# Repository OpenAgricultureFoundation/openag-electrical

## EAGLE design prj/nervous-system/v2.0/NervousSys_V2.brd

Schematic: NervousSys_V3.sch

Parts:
ATTRIBUTES: DOCFIELD
C1: 4.7uF; CAP_C1206
C2: 0.1uF; C0603
C3, C11: .1uF; C0603@1
C4: 4.7uF; C0805
C9: 10uF; C1206
D1: SMAJ14A; DO-214AC
D2, D3, D4: APT1608CGCK; CHIPLED_0603
F11: SST 7; SS
F12: GSH15
IC2, IC3, IC4, IC5, IC6, IC7, IC8, IC9: PCA9615DP; SOP50P490X110-10N
J1: 87583-2010BLF; CONN_USB-87583
J2, J3, J4, J5, J6, J7, J8, J9: 54602-908LF; OPENAG-V1-RJ45
R1, R22, R23, R30, R31, R38, R39, R46, R47, R54, R55, R62, R63, R70, R71, R78, R79: 10K; R0603
R2, R3, R4, R5, R6, R7, R8, R9: 10K; 0603-RES
R10: 200; RC0603N
R11: 560; RC0603N
R12: 4.3K; RC0603N
R13, R86, R87: 0 OHM; RC0603N
R16, R18, R19, R20, R24, R26, R27, R28, R32, R34, R35, R36, R40, R42, R43, R44, R48, R50, R51, R52, R56, R58, R59, R60, R64, R66, R67, R68, R72, R74, R75, R76: 600; R0603
R17, R21, R25, R29, R33, R37, R41, R45, R49, R53, R57, R61, R65, R69, R73, R77: 120; R0603
T1: R-78E5.0-1.0
U1: TCA9548APWRPW24-M; PW24-M
U2: PHOTONH; PHOTON
U$1, U$3: PJ-036AH
U$4: BBB_SMD; 23PINHEADERSMD

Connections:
24V_IN: F11.1, F12.1, U$1.1, U$3.1
+5V: C2.1, C4.1, IC2.10 (VDD_(B)), IC3.10 (VDD_(B)), IC4.10 (VDD_(B)), IC5.10 (VDD_(B)), IC6.10 (VDD_(B)), IC7.10 (VDD_(B)), IC8.10 (VDD_(B)), IC9.10 (VDD_(B)), R11.2, R18.1, R19.2, R26.1, R27.2, R34.1, R35.2, R42.1, R43.2, R50.1, R51.2, R58.1, R59.2, R66.1, R67.2, R74.1, R75.2, T1.3 (+VOUT), U2.1 (VIN), U$4.VDD5V; also elsewhere on the board
A0_EXT_1: R4.1, R5.2, U1.1 (A0)
A1_EXT_1: R6.1, R7.2, U1.2 (A1)
A2_EXT_1: R2.1, R3.2, U1.21 (A2)
DSCLM0: IC2.6 (DSCLM), J2.DSCLM(5) (DSCLM), R20.2, R21.1
DSCLM1: IC3.6 (DSCLM), J3.DSCLM(5) (DSCLM), R28.2, R29.1
DSCLM2: IC5.6 (DSCLM), J5.DSCLM(5) (DSCLM), R44.2, R45.1
DSCLM3: IC4.6 (DSCLM), J4.DSCLM(5) (DSCLM), R36.2, R37.1
DSCLM4: IC6.6 (DSCLM), J6.DSCLM(5) (DSCLM), R52.2, R53.1
DSCLM5: IC7.6 (DSCLM), J7.DSCLM(5) (DSCLM), R60.2, R61.1
DSCLM6: IC8.6 (DSCLM), J8.DSCLM(5) (DSCLM), R68.2, R69.1
DSCLM7: IC9.6 (DSCLM), J9.DSCLM(5) (DSCLM), R76.2, R77.1
DSCLP0: IC2.7 (DSCLP), J2.DSCLP(4) (DSCLP), R19.1, R21.2
DSCLP1: IC3.7 (DSCLP), J3.DSCLP(4) (DSCLP), R27.1, R29.2
DSCLP2: IC5.7 (DSCLP), J5.DSCLP(4) (DSCLP), R43.1, R45.2
DSCLP3: IC4.7 (DSCLP), J4.DSCLP(4) (DSCLP), R35.1, R37.2
DSCLP4: IC6.7 (DSCLP), J6.DSCLP(4) (DSCLP), R51.1, R53.2
DSCLP5: IC7.7 (DSCLP), J7.DSCLP(4) (DSCLP), R59.1, R61.2
DSCLP6: IC8.7 (DSCLP), J8.DSCLP(4) (DSCLP), R67.1, R69.2
DSCLP7: IC9.7 (DSCLP), J9.DSCLP(4) (DSCLP), R75.1, R77.2
DSDAM0: IC2.9 (DSDAM), J2.DSDAM(2) (DSDAM), R16.1, R17.2
DSDAM1: IC3.9 (DSDAM), J3.DSDAM(2) (DSDAM), R24.1, R25.2
DSDAM2: IC5.9 (DSDAM), J5.DSDAM(2) (DSDAM), R40.1, R41.2
DSDAM3: IC4.9 (DSDAM), J4.DSDAM(2) (DSDAM), R32.1, R33.2
DSDAM4: IC6.9 (DSDAM), J6.DSDAM(2) (DSDAM), R48.1, R49.2
DSDAM5: IC7.9 (DSDAM), J7.DSDAM(2) (DSDAM), R56.1, R57.2
DSDAM6: IC8.9 (DSDAM), J8.DSDAM(2) (DSDAM), R64.1, R65.2
DSDAM7: IC9.9 (DSDAM), J9.DSDAM(2) (DSDAM), R72.1, R73.2
DSDAP0: IC2.8 (DSDAP), J2.DSDAP(1) (DSDAP), R17.1, R18.2
DSDAP1: IC3.8 (DSDAP), J3.DSDAP(1) (DSDAP), R25.1, R26.2
DSDAP2: IC5.8 (DSDAP), J5.DSDAP(1) (DSDAP), R41.1, R42.2
DSDAP3: IC4.8 (DSDAP), J4.DSDAP(1) (DSDAP), R33.1, R34.2
DSDAP4: IC6.8 (DSDAP), J6.DSDAP(1) (DSDAP), R49.1, R50.2
DSDAP5: IC7.8 (DSDAP), J7.DSDAP(1) (DSDAP), R57.1, R58.2
DSDAP6: IC8.8 (DSDAP), J8.DSDAP(1) (DSDAP), R65.1, R66.2
DSDAP7: IC9.8 (DSDAP), J9.DSDAP(1) (DSDAP), R73.1, R74.2
GND: C1.2, C2.2, C3.2, C4.2, C9.2, C11.2, D1.A, D2.C, D3.C, D4.C, IC2.5 (VSS), IC3.5 (VSS), IC4.5 (VSS), IC5.5 (VSS), IC6.5 (VSS), IC7.5 (VSS), IC8.5 (VSS), IC9.5 (VSS), J1.1, J2.GND(3) (GND), J3.GND(3) (GND), J4.GND(3) (GND), J5.GND(3) (GND), J6.GND(3) (GND), J7.GND(3) (GND), J8.GND(3) (GND), J9.GND(3) (GND), R3.1, R5.1, R7.1, R16.2, R20.1, R24.2, R28.1, R32.2, R36.1, R40.2, R44.1, R48.2, R52.1, R56.2, R60.1, R64.2, R68.1, R72.2, R76.1, T1.2 (GND), U1.12 (GND), U2.2 (GND), U2.21 (GND), U$1.2, U$1.3, U$3.2, U$3.3, U$4.DGND; also elsewhere on the board
unnamed: D3.A, R11.1
unnamed: D4.A, R12.1
unnamed: D2.A, R10.1
PHOTON_A0: U2.12 (A0)
PHOTON_A1: U2.11 (A1)
PHOTON_D2: U2.15 (D2)
PHOTON_D3: U2.16 (D3)
PHOTON_D4: U2.17 (D4)
PHOTON_RX: U2.4 (RX)
PHOTON_SCL: R87.1, U2.14 (D1)
PHOTON_SDA: R86.1, U2.13 (D0)
PHOTON_TX: U2.3 (TX)
RESET1: R1.1, U1.3 (!RESET)
SC0: IC2.4 (SCL), R23.1, U1.5 (SC0)
SC1: IC3.4 (SCL), R31.1, U1.7 (SC1)
SC2: IC5.4 (SCL), R47.1, U1.9 (SC2)
SC3: IC4.4 (SCL), R39.1, U1.11 (SC3)
SC4: IC6.4 (SCL), R55.1, U1.14 (SC4)
SC5: IC7.4 (SCL), R63.1, U1.16 (SC5)
SC6: IC8.4 (SCL), R71.1, U1.18 (SC6)
SC7: IC9.4 (SCL), R79.1, U1.20 (SC7)
SCL: R8.1, R87.2, U1.22 (SCL); also elsewhere on the board
SD0: IC2.2 (SDA), R22.1, U1.4 (SD0)
SD1: IC3.2 (SDA), R30.1, U1.6 (SD1)
SD2: IC5.2 (SDA), R46.1, U1.8 (SD2)
SD3: IC4.2 (SDA), R38.1, U1.10 (SD3)
SD4: IC6.2 (SDA), R54.1, U1.13 (SD4)
SD5: IC7.2 (SDA), R62.1, U1.15 (SD5)
SD6: IC8.2 (SDA), R70.1, U1.17 (SD6)
SD7: IC9.2 (SDA), R78.1, U1.19 (SD7)
SDA: R9.1, R86.2, U1.23 (SDA); also elsewhere on the board
USBM0: J2.USBM(8) (USBM)
USBM1: J1.3, J3.USBM(8) (USBM)
USBM2: J5.USBM(8) (USBM)
USBM3: J4.USBM(8) (USBM)
USBM4: J6.USBM(8) (USBM)
USBM5: J7.USBM(8) (USBM)
USBM6: J8.USBM(8) (USBM)
USBM7: J9.USBM(8) (USBM)
USBP0: J2.USBP(7) (USBP)
USBP1: J1.2, J3.USBP(7) (USBP)
USBP2: J5.USBP(7) (USBP)
USBP3: J4.USBP(7) (USBP)
USBP4: J6.USBP(7) (USBP)
USBP5: J7.USBP(7) (USBP)
USBP6: J8.USBP(7) (USBP)
USBP7: J9.USBP(7) (USBP)
VBAT: U2.22 (VBAT)

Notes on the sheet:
Original Board by Dan Poitrast
Change Log:
I2C Pull-up Resistors
Released under the Creative Commons Attribution Share-Alike 4.0 License https://creativecommons.org/licenses/by-sa/4.0/
I2C Address Select IO Ext 1
Beaglebone Black Outline and throughholes

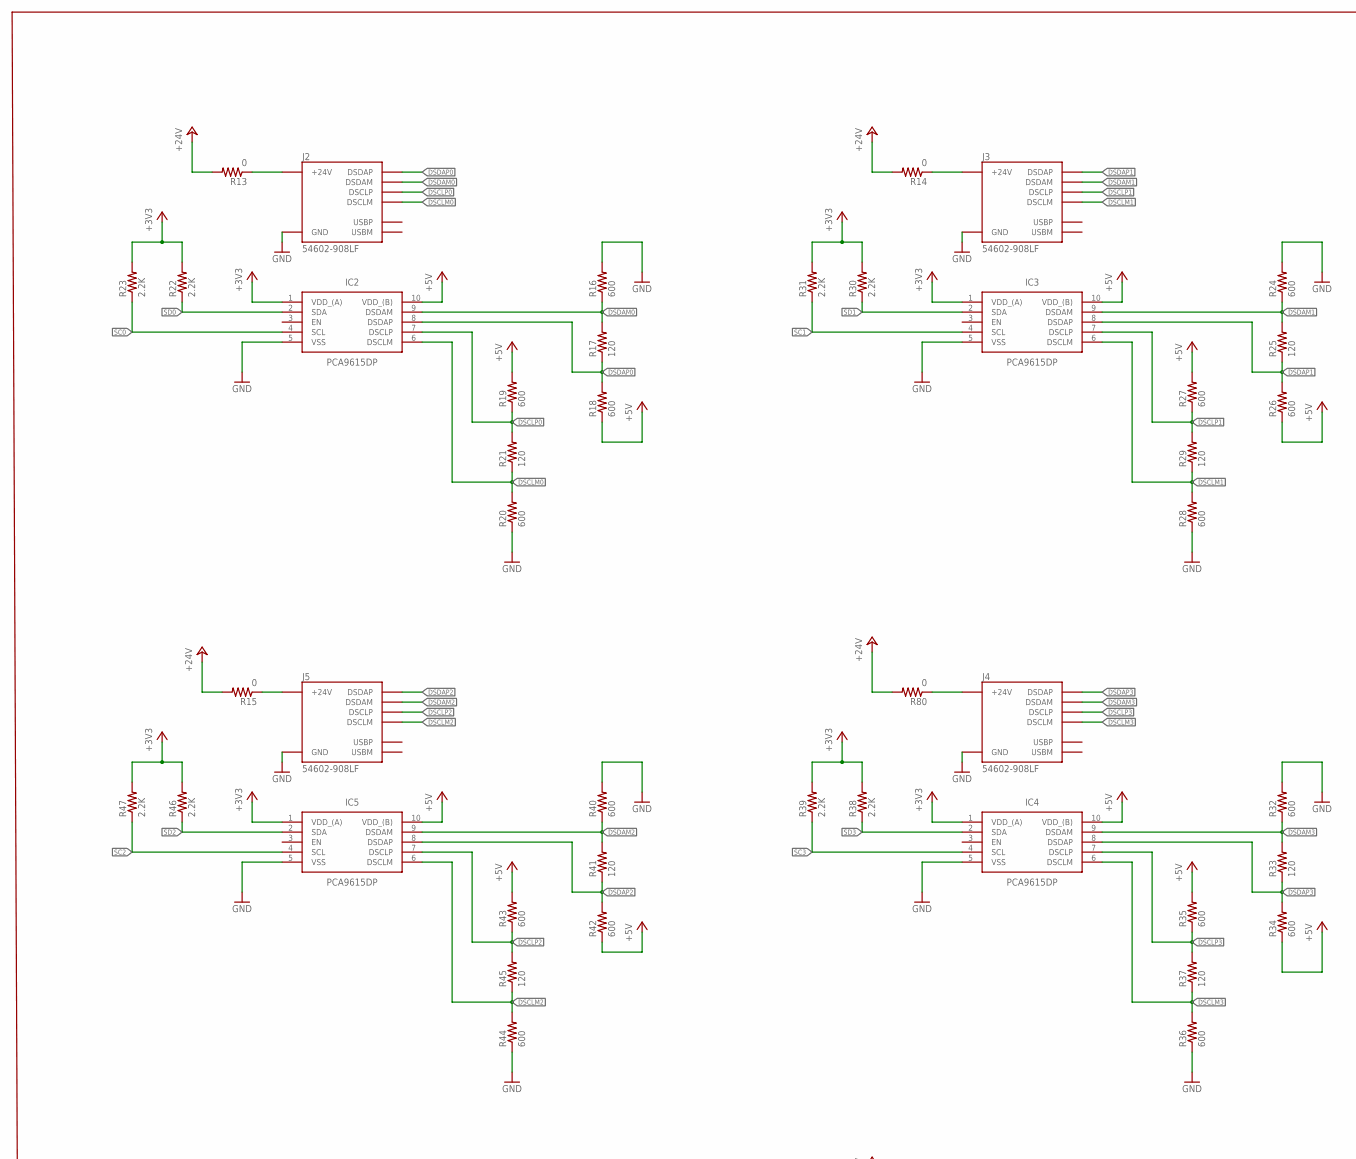
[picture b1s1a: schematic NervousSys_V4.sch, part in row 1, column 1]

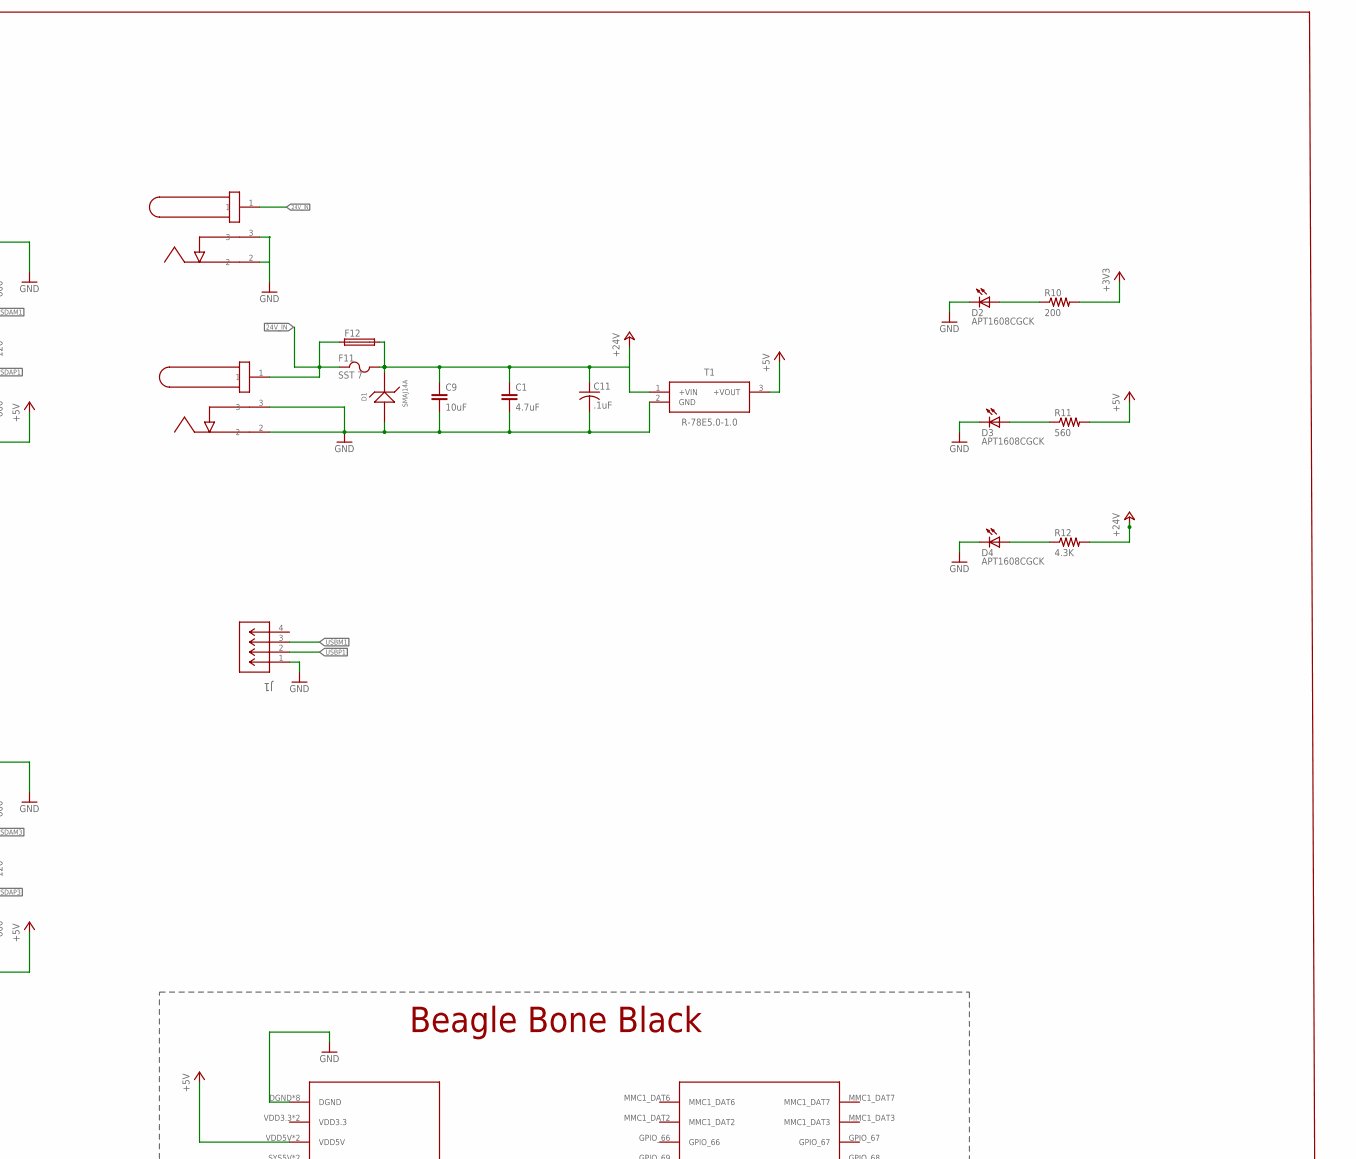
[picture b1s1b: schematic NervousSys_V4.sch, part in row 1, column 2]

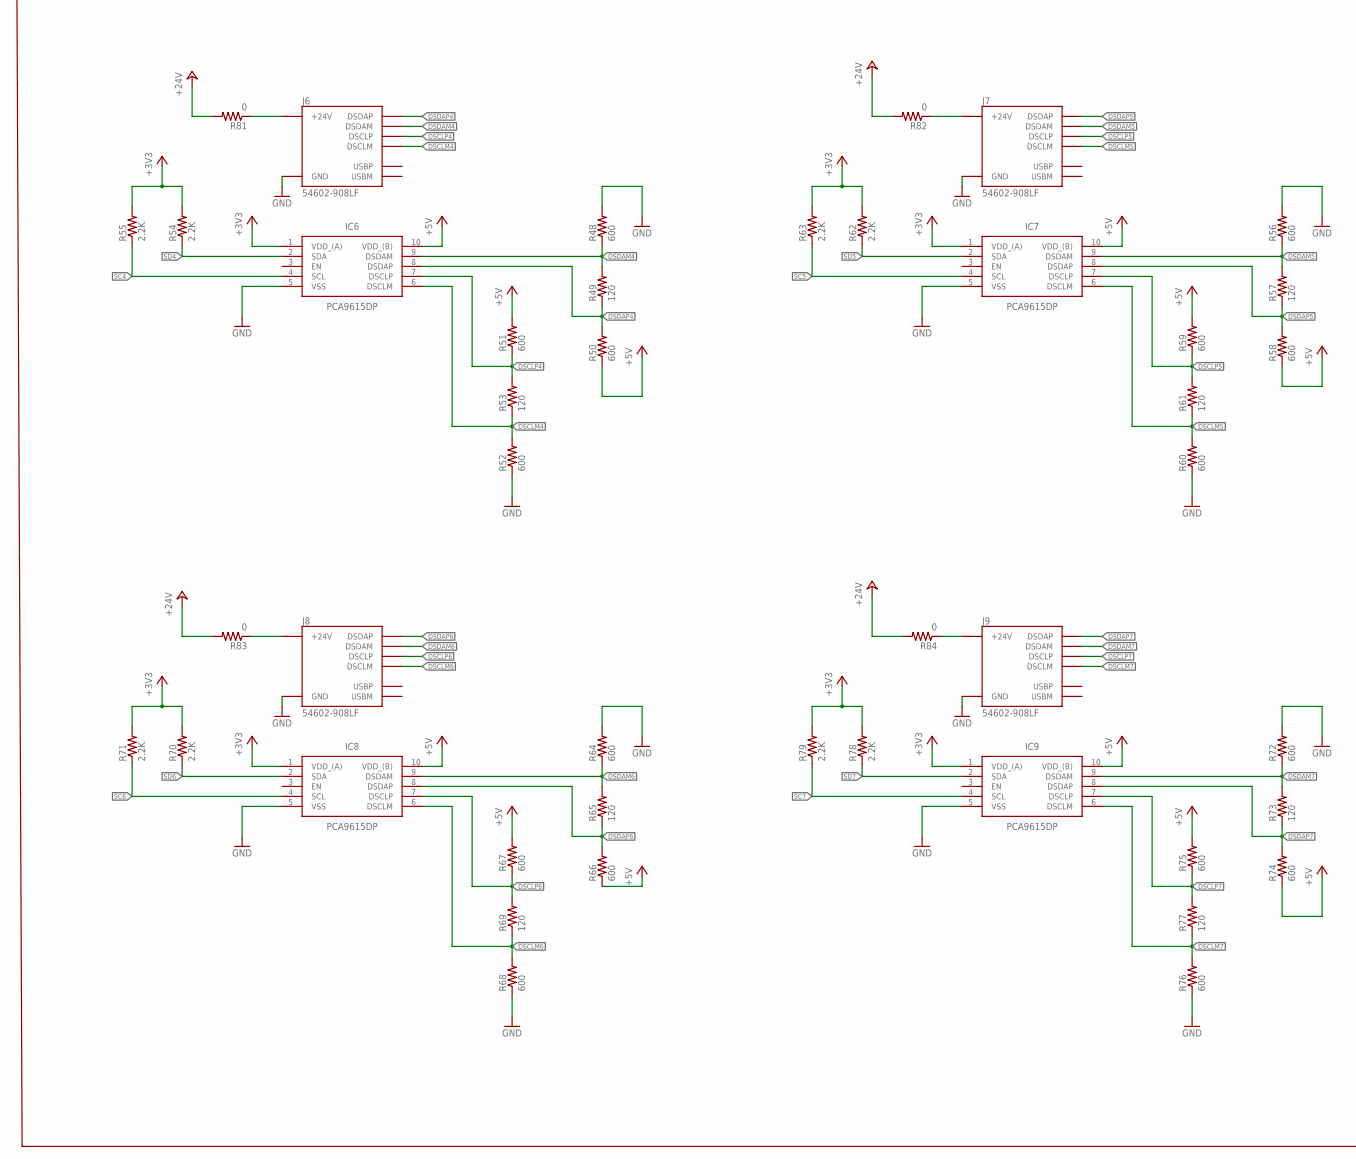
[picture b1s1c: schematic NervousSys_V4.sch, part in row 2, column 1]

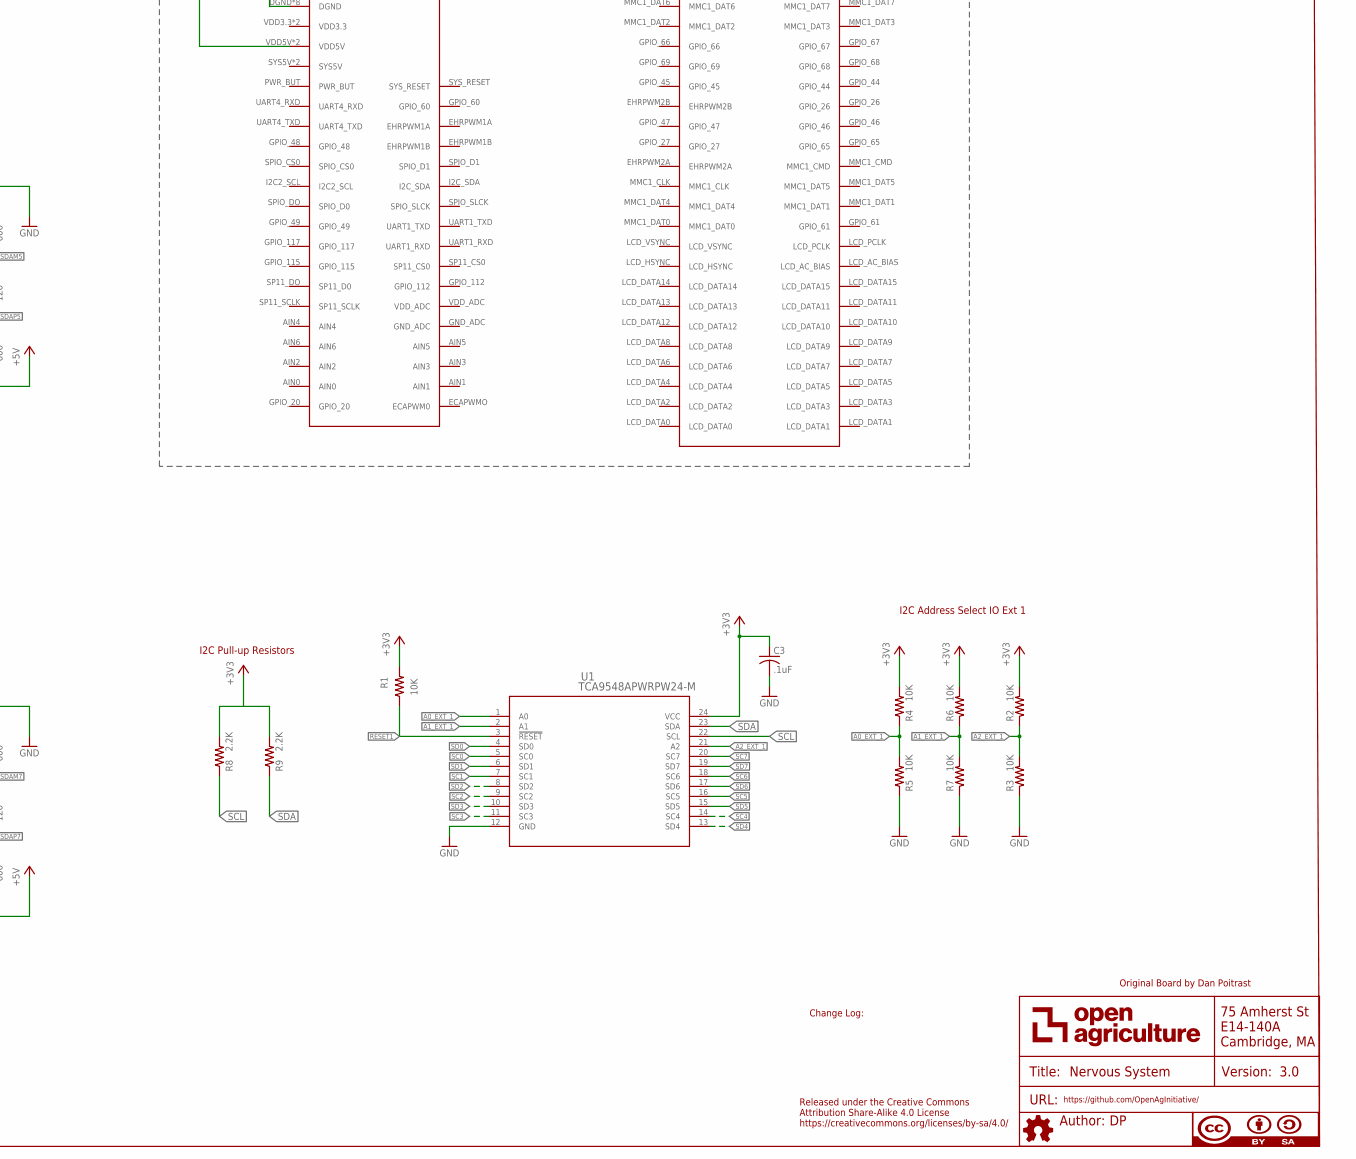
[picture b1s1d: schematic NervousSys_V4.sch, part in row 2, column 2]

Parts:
ATTRIBUTES: DOCFIELD
C1: 4.7uF; CAP_C1206
C3, C11: .1uF; C0603@1
C9: 10uF; C1206
D1: SMAJ14A; DO-214AC
D2, D3, D4: APT1608CGCK; CHIPLED_0603
F11: SST 7; SS
F12: GSH15
IC2, IC3, IC4, IC5, IC6, IC7, IC8, IC9: PCA9615DP; SOP50P490X110-10N
J1: 87583-2010BLF; CONN_USB-87583
J2, J3, J4, J5, J6, J7, J8, J9: 54602-908LF; OPENAG-V1-RJ45
R1: 10K; R0603
R2, R3, R4, R5, R6, R7: 10K; 0603-RES
R8, R9: 2.2K; 0603-RES
R10: 200; RC0603N
R11: 560; RC0603N
R12: 4.3K; RC0603N
R13, R14, R15, R80, R81, R82, R83, R84: 0; R0603
R16, R18, R19, R20, R24, R26, R27, R28, R32, R34, R35, R36, R40, R42, R43, R44, R48, R50, R51, R52, R56, R58, R59, R60, R64, R66, R67, R68, R72, R74, R75, R76: 600; R0603
R17, R21, R25, R29, R33, R37, R41, R45, R49, R53, R57, R61, R65, R69, R73, R77: 120; R0603
R22, R23, R30, R31, R38, R39, R46, R47, R54, R55, R62, R63, R70, R71, R78, R79: 2.2K; R0603
T1: R-78E5.0-1.0
U1: TCA9548APWRPW24-M; PW24-M
U$1, U$3: PJ-036AH
U$4: BBB_SMD; 23PINHEADERSMD

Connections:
24V_IN: F11.1, F12.1, U$1.1, U$3.1
+5V: IC2.10 (VDD_(B)), IC3.10 (VDD_(B)), IC4.10 (VDD_(B)), IC5.10 (VDD_(B)), IC6.10 (VDD_(B)), IC7.10 (VDD_(B)), IC8.10 (VDD_(B)), IC9.10 (VDD_(B)), R11.2, R18.1, R19.2, R26.1, R27.2, R34.1, R35.2, R42.1, R43.2, R50.1, R51.2, R58.1, R59.2, R66.1, R67.2, R74.1, R75.2, T1.3 (+VOUT), U$4.VDD5V; also elsewhere on the board
A0_EXT_1: R4.1, R5.2, U1.1 (A0)
A1_EXT_1: R6.1, R7.2, U1.2 (A1)
A2_EXT_1: R2.1, R3.2, U1.21 (A2)
DSCLM0: IC2.6 (DSCLM), J2.DSCLM(5) (DSCLM), R20.2, R21.1
DSCLM1: IC3.6 (DSCLM), J3.DSCLM(5) (DSCLM), R28.2, R29.1
DSCLM2: IC5.6 (DSCLM), J5.DSCLM(5) (DSCLM), R44.2, R45.1
DSCLM3: IC4.6 (DSCLM), J4.DSCLM(5) (DSCLM), R36.2, R37.1
DSCLM4: IC6.6 (DSCLM), J6.DSCLM(5) (DSCLM), R52.2, R53.1
DSCLM5: IC7.6 (DSCLM), J7.DSCLM(5) (DSCLM), R60.2, R61.1
DSCLM6: IC8.6 (DSCLM), J8.DSCLM(5) (DSCLM), R68.2, R69.1
DSCLM7: IC9.6 (DSCLM), J9.DSCLM(5) (DSCLM), R76.2, R77.1
DSCLP0: IC2.7 (DSCLP), J2.DSCLP(4) (DSCLP), R19.1, R21.2
DSCLP1: IC3.7 (DSCLP), J3.DSCLP(4) (DSCLP), R27.1, R29.2
DSCLP2: IC5.7 (DSCLP), J5.DSCLP(4) (DSCLP), R43.1, R45.2
DSCLP3: IC4.7 (DSCLP), J4.DSCLP(4) (DSCLP), R35.1, R37.2
DSCLP4: IC6.7 (DSCLP), J6.DSCLP(4) (DSCLP), R51.1, R53.2
DSCLP5: IC7.7 (DSCLP), J7.DSCLP(4) (DSCLP), R59.1, R61.2
DSCLP6: IC8.7 (DSCLP), J8.DSCLP(4) (DSCLP), R67.1, R69.2
DSCLP7: IC9.7 (DSCLP), J9.DSCLP(4) (DSCLP), R75.1, R77.2
DSDAM0: IC2.9 (DSDAM), J2.DSDAM(2) (DSDAM), R16.1, R17.2
DSDAM1: IC3.9 (DSDAM), J3.DSDAM(2) (DSDAM), R24.1, R25.2
DSDAM2: IC5.9 (DSDAM), J5.DSDAM(2) (DSDAM), R40.1, R41.2
DSDAM3: IC4.9 (DSDAM), J4.DSDAM(2) (DSDAM), R32.1, R33.2
DSDAM4: IC6.9 (DSDAM), J6.DSDAM(2) (DSDAM), R48.1, R49.2
DSDAM5: IC7.9 (DSDAM), J7.DSDAM(2) (DSDAM), R56.1, R57.2
DSDAM6: IC8.9 (DSDAM), J8.DSDAM(2) (DSDAM), R64.1, R65.2
DSDAM7: IC9.9 (DSDAM), J9.DSDAM(2) (DSDAM), R72.1, R73.2
DSDAP0: IC2.8 (DSDAP), J2.DSDAP(1) (DSDAP), R17.1, R18.2
DSDAP1: IC3.8 (DSDAP), J3.DSDAP(1) (DSDAP), R25.1, R26.2
DSDAP2: IC5.8 (DSDAP), J5.DSDAP(1) (DSDAP), R41.1, R42.2
DSDAP3: IC4.8 (DSDAP), J4.DSDAP(1) (DSDAP), R33.1, R34.2
DSDAP4: IC6.8 (DSDAP), J6.DSDAP(1) (DSDAP), R49.1, R50.2
DSDAP5: IC7.8 (DSDAP), J7.DSDAP(1) (DSDAP), R57.1, R58.2
DSDAP6: IC8.8 (DSDAP), J8.DSDAP(1) (DSDAP), R65.1, R66.2
DSDAP7: IC9.8 (DSDAP), J9.DSDAP(1) (DSDAP), R73.1, R74.2
GND: C1.2, C3.2, C9.2, C11.2, D1.A, D2.C, D3.C, D4.C, IC2.5 (VSS), IC3.5 (VSS), IC4.5 (VSS), IC5.5 (VSS), IC6.5 (VSS), IC7.5 (VSS), IC8.5 (VSS), IC9.5 (VSS), J1.1, J2.GND(3) (GND), J3.GND(3) (GND), J4.GND(3) (GND), J5.GND(3) (GND), J6.GND(3) (GND), J7.GND(3) (GND), J8.GND(3) (GND), J9.GND(3) (GND), R3.1, R5.1, R7.1, R16.2, R20.1, R24.2, R28.1, R32.2, R36.1, R40.2, R44.1, R48.2, R52.1, R56.2, R60.1, R64.2, R68.1, R72.2, R76.1, T1.2 (GND), U1.12 (GND), U$1.2, U$1.3, U$3.2, U$3.3, U$4.DGND; also elsewhere on the board
unnamed: D3.A, R11.1
unnamed: D4.A, R12.1
unnamed: D2.A, R10.1
RESET1: R1.1, U1.3 (!RESET)
SC0: IC2.4 (SCL), R23.1, U1.5 (SC0)
SC1: IC3.4 (SCL), R31.1, U1.7 (SC1)
SC2: IC5.4 (SCL), R47.1, U1.9 (SC2)
SC3: IC4.4 (SCL), R39.1, U1.11 (SC3)
SC4: IC6.4 (SCL), R55.1, U1.14 (SC4)
SC5: IC7.4 (SCL), R63.1, U1.16 (SC5)
SC6: IC8.4 (SCL), R71.1, U1.18 (SC6)
SC7: IC9.4 (SCL), R79.1, U1.20 (SC7)
SCL: R8.1, U1.22 (SCL); also elsewhere on the board
SD0: IC2.2 (SDA), R22.1, U1.4 (SD0)
SD1: IC3.2 (SDA), R30.1, U1.6 (SD1)
SD2: IC5.2 (SDA), R46.1, U1.8 (SD2)
SD3: IC4.2 (SDA), R38.1, U1.10 (SD3)
SD4: IC6.2 (SDA), R54.1, U1.13 (SD4)
SD5: IC7.2 (SDA), R62.1, U1.15 (SD5)
SD6: IC8.2 (SDA), R70.1, U1.17 (SD6)
SD7: IC9.2 (SDA), R78.1, U1.19 (SD7)
SDA: R9.1, U1.23 (SDA); also elsewhere on the board
USBM1: J1.3; also elsewhere on the board
USBP1: J1.2; also elsewhere on the board

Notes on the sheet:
Original Board by Dan Poitrast
Change Log:
I2C Pull-up Resistors
Released under the Creative Commons Attribution Share-Alike 4.0 License https://creativecommons.org/licenses/by-sa/4.0/
I2C Address Select IO Ext 1

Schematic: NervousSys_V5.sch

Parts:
ATTRIBUTES: DOCFIELD
C1: 4.7uF; CAP_C1206
C3, C11: .1uF; C0603@1
C9: 10uF; C1206
D1: SMAJ14A; DO-214AC
D2, D3, D4: APT1608CGCK; CHIPLED_0603
F11: SST 7; SS
F12: GSH15
IC2, IC3, IC4, IC5: PCA9615DP; SOP50P490X110-10N
J1: 87583-2010BLF; CONN_USB-87583
J2, J3, J4, J5: 54602-908LF; OPENAG-V1-RJ45
R1, R22, R23, R30, R31, R38, R39, R46, R47: 10K; R0603
R2, R3, R4, R5, R6, R7, R8, R9: 10K; 0603-RES
R10: 200; RC0603N
R11: 560; RC0603N
R12: 4.3K; RC0603N
R16, R18, R19, R20, R24, R26, R27, R28, R32, R34, R35, R36, R40, R42, R43, R44: 600; R0603
R17, R21, R25, R29, R33, R37, R41, R45: 120; R0603
SV1: FE20-2
T1: R-78E5.0-1.0
U1: TCA9548APWRPW24-M; PW24-M
U$1, U$3: PJ-036AH

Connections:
24V_IN: F11.1, F12.1, U$1.1, U$3.1
+5V: IC2.10 (VDD_(B)), IC3.10 (VDD_(B)), IC4.10 (VDD_(B)), IC5.10 (VDD_(B)), R11.2, R18.1, R19.2, R26.1, R27.2, R34.1, R35.2, R42.1, R43.2, SV1.2, SV1.4, T1.3 (+VOUT); also elsewhere on the board
A0_EXT_1: R4.1, R5.2, U1.1 (A0)
A1_EXT_1: R6.1, R7.2, U1.2 (A1)
A2_EXT_1: R2.1, R3.2, U1.21 (A2)
DSCLM0: IC2.6 (DSCLM), J2.DSCLM(5) (DSCLM), R20.2, R21.1
DSCLM1: IC3.6 (DSCLM), J3.DSCLM(5) (DSCLM), R28.2, R29.1
DSCLM2: IC5.6 (DSCLM), J5.DSCLM(5) (DSCLM), R44.2, R45.1
DSCLM3: IC4.6 (DSCLM), J4.DSCLM(5) (DSCLM), R36.2, R37.1
DSCLP0: IC2.7 (DSCLP), J2.DSCLP(4) (DSCLP), R19.1, R21.2
DSCLP1: IC3.7 (DSCLP), J3.DSCLP(4) (DSCLP), R27.1, R29.2
DSCLP2: IC5.7 (DSCLP), J5.DSCLP(4) (DSCLP), R43.1, R45.2
DSCLP3: IC4.7 (DSCLP), J4.DSCLP(4) (DSCLP), R35.1, R37.2
DSDAM0: IC2.9 (DSDAM), J2.DSDAM(2) (DSDAM), R16.1, R17.2
DSDAM1: IC3.9 (DSDAM), J3.DSDAM(2) (DSDAM), R24.1, R25.2
DSDAM2: IC5.9 (DSDAM), J5.DSDAM(2) (DSDAM), R40.1, R41.2
DSDAM3: IC4.9 (DSDAM), J4.DSDAM(2) (DSDAM), R32.1, R33.2
DSDAP0: IC2.8 (DSDAP), J2.DSDAP(1) (DSDAP), R17.1, R18.2
DSDAP1: IC3.8 (DSDAP), J3.DSDAP(1) (DSDAP), R25.1, R26.2
DSDAP2: IC5.8 (DSDAP), J5.DSDAP(1) (DSDAP), R41.1, R42.2
DSDAP3: IC4.8 (DSDAP), J4.DSDAP(1) (DSDAP), R33.1, R34.2
GND: C1.2, C3.2, C9.2, C11.2, D1.A, D2.C, D3.C, D4.C, IC2.5 (VSS), IC3.5 (VSS), IC4.5 (VSS), IC5.5 (VSS), J1.1, J2.GND(3) (GND), J3.GND(3) (GND), J4.GND(3) (GND), J5.GND(3) (GND), R3.1, R5.1, R7.1, R16.2, R20.1, R24.2, R28.1, R32.2, R36.1, R40.2, R44.1, SV1.6, SV1.9, SV1.14, SV1.20, SV1.25, SV1.30, SV1.34, SV1.39, T1.2 (GND), U1.12 (GND), U$1.2, U$1.3, U$3.2, U$3.3; also elsewhere on the board
unnamed: D3.A, R11.1
unnamed: D4.A, R12.1
unnamed: D2.A, R10.1
RESET1: R1.1, U1.3 (!RESET)
SC0: IC2.4 (SCL), R23.1, U1.5 (SC0)
SC1: IC3.4 (SCL), R31.1, U1.7 (SC1)
SC2: IC5.4 (SCL), R47.1, U1.9 (SC2)
SC3: IC4.4 (SCL), R39.1, U1.11 (SC3)
SC4: U1.14 (SC4); also elsewhere on the board
SC5: U1.16 (SC5); also elsewhere on the board
SC6: U1.18 (SC6); also elsewhere on the board
SC7: U1.20 (SC7); also elsewhere on the board
SCL: R8.1, SV1.28, U1.22 (SCL); also elsewhere on the board
SD0: IC2.2 (SDA), R22.1, U1.4 (SD0)
SD1: IC3.2 (SDA), R30.1, U1.6 (SD1)
SD2: IC5.2 (SDA), R46.1, U1.8 (SD2)
SD3: IC4.2 (SDA), R38.1, U1.10 (SD3)
SD4: U1.13 (SD4); also elsewhere on the board
SD5: U1.15 (SD5); also elsewhere on the board
SD6: U1.17 (SD6); also elsewhere on the board
SD7: U1.19 (SD7); also elsewhere on the board
SDA: R9.1, SV1.27, U1.23 (SDA); also elsewhere on the board
USBM0: J2.USBM(8) (USBM)
USBM1: J1.3, J3.USBM(8) (USBM)
USBM2: J5.USBM(8) (USBM)
USBM3: J4.USBM(8) (USBM)
USBP0: J2.USBP(7) (USBP)
USBP1: J1.2, J3.USBP(7) (USBP)
USBP2: J5.USBP(7) (USBP)
USBP3: J4.USBP(7) (USBP)

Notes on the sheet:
Original Board by Dan Poitrast
Change Log:
I2C Pull-up Resistors
Released under the Creative Commons Attribution Share-Alike 4.0 License https://creativecommons.org/licenses/by-sa/4.0/
I2C Address Select IO Ext 1
Beaglebone Black Outline and throughholes

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
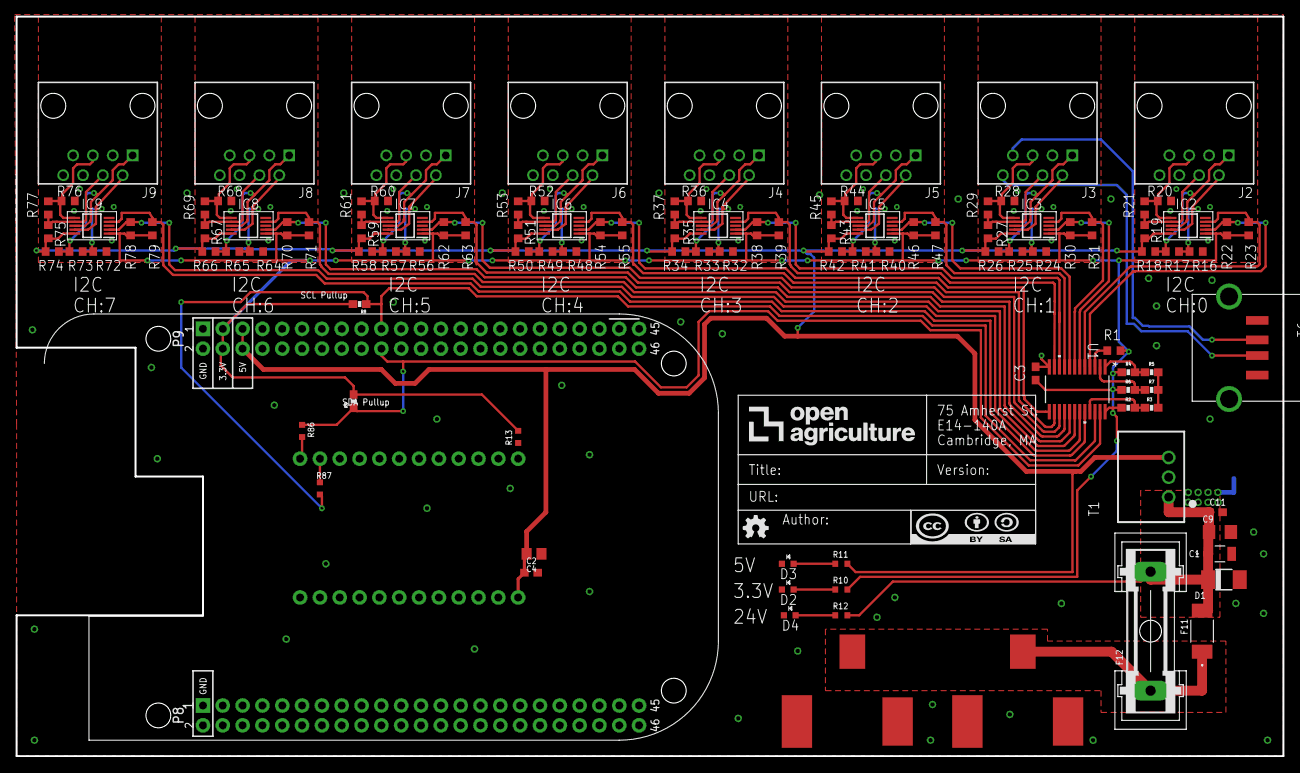
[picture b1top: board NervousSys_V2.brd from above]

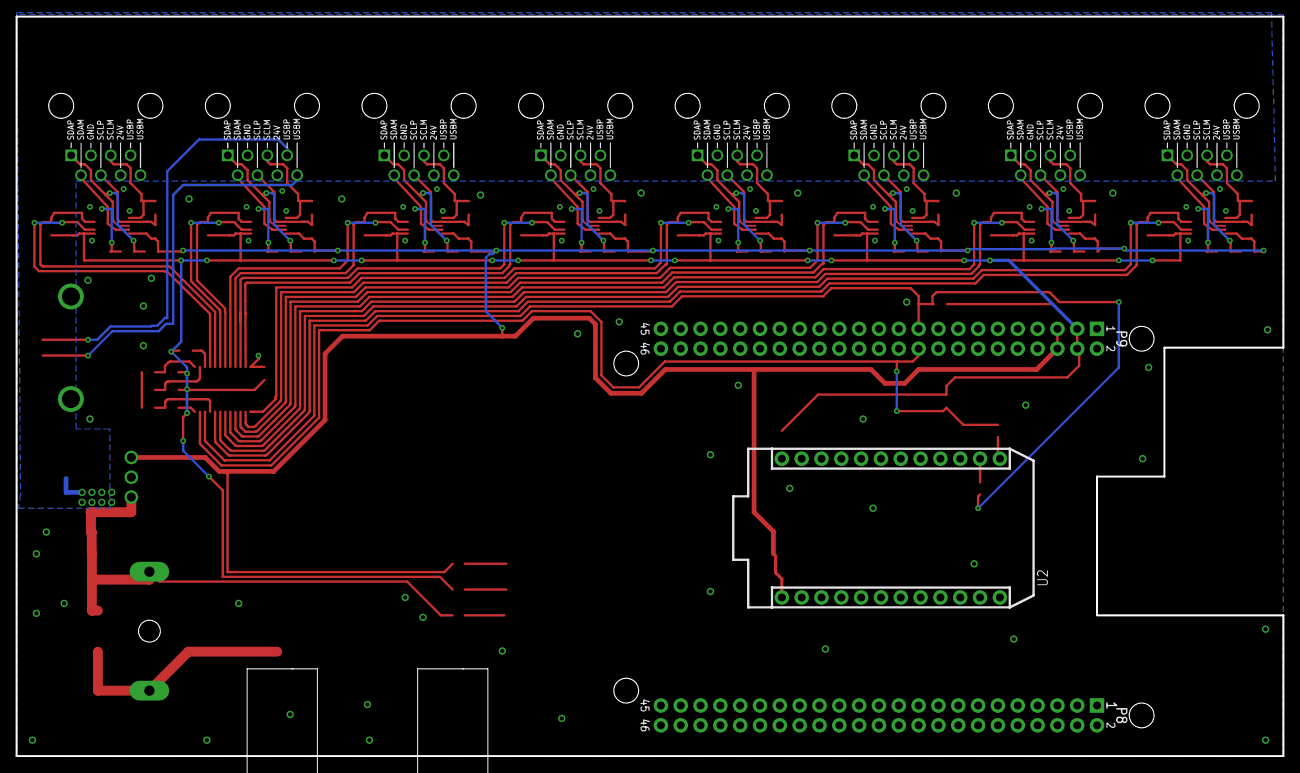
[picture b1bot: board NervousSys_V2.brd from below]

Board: 2 copper layers, 162.3 x 94.7 mm, 115 parts (2 on the bottom side), 67 nets.

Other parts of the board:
U$2: BEAGLE_BONE_BLACK_CAPE

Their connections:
+5V: U$2.P9.5, U$2.P9.6; also elsewhere on the board
GND: U$2.P8.1, U$2.P8.2, U$2.P9.1, U$2.P9.2, U$2.P9.43, U$2.P9.44, U$2.P9.45, U$2.P9.46; also elsewhere on the board
SCL: U$2.P9.19; also elsewhere on the board
SDA: U$2.P9.20; also elsewhere on the board

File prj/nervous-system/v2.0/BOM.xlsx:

Part | Value | Device | Package | Description | Column1 | Column2 | Column3 | Column4 | Column5 | Column6 | Column7 | Column8 | Column9 | Column10 | Column11 | Column12 | Column13 | Column14 | Column15 | Column16 | Column17 | Column18 | Column19 | Column20 | Column21 | Column22 | Column23 | Column24 | Column25
F12 |  | GSH15 | GSH15 | Fuse Holder
C3 | .1uF | C-USC0603 | C0603@1 | 50V or greater
C11 | .1uF | C-USC0603 | C0603@1 | 50V or greater
R1 | 10K | R-US_R0603 | R0603 | 5% tolerance or greater, 1/10W, 0603
R2 | 10K | R-US_R0603 | 0603-RES | 5% tolerance or greater, 1/10W, 0603
R4 | 10K | R-US_R0603 | 0603-RES | 5% tolerance or greater, 1/10W, 0603
R6 | 10K | R-US_R0603 | 0603-RES | 5% tolerance or greater, 1/10W, 0603
R8 | 10K | R-US_R0603 | 0603-RES | 5% tolerance or greater, 1/10W, 0603
R9 | 10K | R-US_R0603 | 0603-RES | 5% tolerance or greater, 1/10W, 0603
R22 | 10K | R-US_R0603 | R0603 | 5% tolerance or greater, 1/10W, 0603
R23 | 10K | R-US_R0603 | R0603 | 5% tolerance or greater, 1/10W, 0604
R30 | 10K | R-US_R0603 | R0603 | 5% tolerance or greater, 1/10W, 0605
R31 | 10K | R-US_R0603 | R0603 | 5% tolerance or greater, 1/10W, 0606
R38 | 10K | R-US_R0603 | R0603 | 5% tolerance or greater, 1/10W, 0607
R39 | 10K | R-US_R0603 | R0603 | 5% tolerance or greater, 1/10W, 0608
R46 | 10K | R-US_R0603 | R0603 | 5% tolerance or greater, 1/10W, 0609
R47 | 10K | R-US_R0603 | R0603 | 5% tolerance or greater, 1/10W, 0610
R54 | 10K | R-US_R0603 | R0603 | 5% tolerance or greater, 1/10W, 0611
R55 | 10K | R-US_R0603 | R0603 | 5% tolerance or greater, 1/10W, 0612
R62 | 10K | R-US_R0603 | R0603 | 5% tolerance or greater, 1/10W, 0613
R63 | 10K | R-US_R0603 | R0603 | 5% tolerance or greater, 1/10W, 0614
R70 | 10K | R-US_R0603 | R0603 | 5% tolerance or greater, 1/10W, 0615
R71 | 10K | R-US_R0603 | R0603 | 5% tolerance or greater, 1/10W, 0616
R78 | 10K | R-US_R0603 | R0603 | 5% tolerance or greater, 1/10W, 0617
R79 | 10K | R-US_R0603 | R0603 | 5% tolerance or greater, 1/10W, 0618
C9 | 10uF | C_US_1206 | C1206 | 50V or greater
R17 | 120 | R-US_R0603 | R0603 | 5% tolerance or greater, 1/10W, 0603
R21 | 120 | R-US_R0603 | R0603 | 5% tolerance or greater, 1/10W, 0604
R25 | 120 | R-US_R0603 | R0603 | 5% tolerance or greater, 1/10W, 0605
R29 | 120 | R-US_R0603 | R0603 | 5% tolerance or greater, 1/10W, 0606
R33 | 120 | R-US_R0603 | R0603 | 5% tolerance or greater, 1/10W, 0607
R37 | 120 | R-US_R0603 | R0603 | 5% tolerance or greater, 1/10W, 0608
R41 | 120 | R-US_R0603 | R0603 | 5% tolerance or greater, 1/10W, 0609
R45 | 120 | R-US_R0603 | R0603 | 5% tolerance or greater, 1/10W, 0610
R49 | 120 | R-US_R0603 | R0603 | 5% tolerance or greater, 1/10W, 0611
R53 | 120 | R-US_R0603 | R0603 | 5% tolerance or greater, 1/10W, 0612
R57 | 120 | R-US_R0603 | R0603 | 5% tolerance or greater, 1/10W, 0613
R61 | 120 | R-US_R0603 | R0603 | 5% tolerance or greater, 1/10W, 0614
R65 | 120 | R-US_R0603 | R0603 | 5% tolerance or greater, 1/10W, 0615
R69 | 120 | R-US_R0603 | R0603 | 5% tolerance or greater, 1/10W, 0616
R73 | 120 | R-US_R0603 | R0603 | 5% tolerance or greater, 1/10W, 0617
R77 | 120 | R-US_R0603 | R0603 | 5% tolerance or greater, 1/10W, 0618
R10 | 200 | R-US_R0603 | RC0603N | 5% tolerance or greater, .25W, 0603
R12 | 4.3K | R-US_R0603 | RC0603N | 5% tolerance or greater, .25W, 0603
J2 | 54602-908LF | OPENAG-V1-RJ45PTH | OPENAG-V1-RJ45 | RJ45 Connector
J3 | 54602-908LF | OPENAG-V1-RJ45PTH | OPENAG-V1-RJ45 | RJ45 Connector
J4 | 54602-908LF | OPENAG-V1-RJ45PTH | OPENAG-V1-RJ45 | RJ45 Connector
J5 | 54602-908LF | OPENAG-V1-RJ45PTH | OPENAG-V1-RJ45 | RJ45 Connector
J6 | 54602-908LF | OPENAG-V1-RJ45PTH | OPENAG-V1-RJ45 | RJ45 Connector
J7 | 54602-908LF | OPENAG-V1-RJ45PTH | OPENAG-V1-RJ45 | RJ45 Connector
J8 | 54602-908LF | OPENAG-V1-RJ45PTH | OPENAG-V1-RJ45 | RJ45 Connector
J9 | 54602-908LF | OPENAG-V1-RJ45PTH | OPENAG-V1-RJ45 | RJ45 Connector
R11 | 560 | R-US_R0603 | RC0603N | 5% tolerance or greater, .25W, 0603
R16 | 600 | R-US_R0603 | R0603 | 5% tolerance or greater, 1/10W, 0603
R18 | 600 | R-US_R0603 | R0603 | 5% tolerance or greater, 1/10W, 0604
R19 | 600 | R-US_R0603 | R0603 | 5% tolerance or greater, 1/10W, 0605
R20 | 600 | R-US_R0603 | R0603 | 5% tolerance or greater, 1/10W, 0606
R24 | 600 | R-US_R0603 | R0603 | 5% tolerance or greater, 1/10W, 0607
R26 | 600 | R-US_R0603 | R0603 | 5% tolerance or greater, 1/10W, 0608
R27 | 600 | R-US_R0603 | R0603 | 5% tolerance or greater, 1/10W, 0609
R28 | 600 | R-US_R0603 | R0603 | 5% tolerance or greater, 1/10W, 0610
R32 | 600 | R-US_R0603 | R0603 | 5% tolerance or greater, 1/10W, 0611
R34 | 600 | R-US_R0603 | R0603 | 5% tolerance or greater, 1/10W, 0612
R35 | 600 | R-US_R0603 | R0603 | 5% tolerance or greater, 1/10W, 0613
R36 | 600 | R-US_R0603 | R0603 | 5% tolerance or greater, 1/10W, 0614
R40 | 600 | R-US_R0603 | R0603 | 5% tolerance or greater, 1/10W, 0615
R42 | 600 | R-US_R0603 | R0603 | 5% tolerance or greater, 1/10W, 0616
R43 | 600 | R-US_R0603 | R0603 | 5% tolerance or greater, 1/10W, 0617
R44 | 600 | R-US_R0603 | R0603 | 5% tolerance or greater, 1/10W, 0618
R48 | 600 | R-US_R0603 | R0603 | 5% tolerance or greater, 1/10W, 0619
R50 | 600 | R-US_R0603 | R0603 | 5% tolerance or greater, 1/10W, 0620
R51 | 600 | R-US_R0603 | R0603 | 5% tolerance or greater, 1/10W, 0621
R52 | 600 | R-US_R0603 | R0603 | 5% tolerance or greater, 1/10W, 0622
R56 | 600 | R-US_R0603 | R0603 | 5% tolerance or greater, 1/10W, 0623
R58 | 600 | R-US_R0603 | R0603 | 5% tolerance or greater, 1/10W, 0624
R59 | 600 | R-US_R0603 | R0603 | 5% tolerance or greater, 1/10W, 0625
R60 | 600 | R-US_R0603 | R0603 | 5% tolerance or greater, 1/10W, 0626
R64 | 600 | R-US_R0603 | R0603 | 5% tolerance or greater, 1/10W, 0627
R66 | 600 | R-US_R0603 | R0603 | 5% tolerance or greater, 1/10W, 0628
R67 | 600 | R-US_R0603 | R0603 | 5% tolerance or greater, 1/10W, 0629
R68 | 600 | R-US_R0603 | R0603 | 5% tolerance or greater, 1/10W, 0630
R72 | 600 | R-US_R0603 | R0603 | 5% tolerance or greater, 1/10W, 0631
R74 | 600 | R-US_R0603 | R0603 | 5% tolerance or greater, 1/10W, 0632
R75 | 600 | R-US_R0603 | R0603 | 5% tolerance or greater, 1/10W, 0633
R76 | 600 | R-US_R0603 | R0603 | 5% tolerance or greater, 1/10W, 0634
J1 | 87583-2010BLF | 87583-2010BLF | CONN_USB-87583 | USB Connector
D2 | APT1608CGCK | APT1608CGCK | CHIPLED_0603 | Indicator LED Green
D3 | APT1608CGCK | APT1608CGCK | CHIPLED_0603 | Indicator LED Green
D4 | APT1608CGCK | APT1608CGCK | CHIPLED_0603 | Indicator LED Green
IC2 | PCA9615DP | PCA9615DP | SOP50P490X110-10N | Buffer IC
IC3 | PCA9615DP | PCA9615DP | SOP50P490X110-10N | Buffer IC
IC4 | PCA9615DP | PCA9615DP | SOP50P490X110-10N | Buffer IC
IC5 | PCA9615DP | PCA9615DP | SOP50P490X110-10N | Buffer IC
IC6 | PCA9615DP | PCA9615DP | SOP50P490X110-10N | Buffer IC
IC7 | PCA9615DP | PCA9615DP | SOP50P490X110-10N | Buffer IC
IC8 | PCA9615DP | PCA9615DP | SOP50P490X110-10N | Buffer IC
IC9 | PCA9615DP | PCA9615DP | SOP50P490X110-10N | Buffer IC
U$1 | PJ-036AH | PJ-036AH | PJ-036AH | 2.1mm Barrel Connector
U$3 | PJ-036AH | PJ-036AH | PJ-036AH | 2.1mm Barrel Connector
T1 | R-78E5.0-1.0 | R-78E5.0-1.0 | R-78E5.0-1.0 | 5V Regulator
U1 | TCA9548APWRPW24-M | TCA9548APWRPW24-M | PW24-M | I2C Mux
Pins | 1528-2021-ND | Pin Header | Pin Header | 2 NEEDED 2:23 .1" spacing can be equivalent component

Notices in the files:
parts and their libraries:
SparkFun-Resistors: Licensing: Creative Commons ShareAlike 4.0 International - https://creativecommons.org/licenses/by-sa/4.0
SparkFun-Boards: Licensing: CC v3.0 Share-Alike You are welcome to use this library for commercial purposes.
